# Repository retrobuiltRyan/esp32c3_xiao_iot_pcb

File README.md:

# esp32c3_xiao_iot_pcb
PCB for MQTT projects. Sensor, I2C screen, rotary encoder input, RGB LEDs, and buck converter breakout for the ESP32 C3 XIAO dev board.

| Project Difficulty | Rating |
|----------|--------|
| **Hardware Difficulty** | ●● Easy |
| **Software Complexity** | ●● Easy? | 

 <br>
This is the ~$5 [ESP32c3 XIAO microcontroller](https://www.digikey.com/en/products/detail/seeed-technology-co-ltd/113991054/16652880) (with its antenna on the left) variant.

### Example Projects

Three-ish example projects are shown using this PCB:

- 1.1 – WiFi Clock
- 1.2 – Basic "Dumb" Clock
- 1.3 – Countdown Timer
- 2.0 – Weather Station with Terminal-Style Display
- 3.0 – Current (120V AC) Probe Monitor over MQTT

## 1.1 WiFi Clock
 <br>
 <br>

Large digit (70mm height) 7-segment clock. Connects to 2.4 GHz WiFi and grabs time from HTTP "google.com" TCP port 80. Previously grabbed time from NTP, but I have found some enterprise networks do not like this traffic and block the device.  

Files for the [RGB LED 7-segment digit PCB](https://github.com/retrobuiltRyan/Neo7Segment-Design-Files). You'll need to make four (each digit needs qty 29 RGB LEDs).  

A Daylight Saving Time function is implemented; however, every 6 months I find this doesn't work as expected, and 6 months between bug testing is annoying, so YMMV. DST compensation works better on Network Time Protocol grabs, but again, some networks do not like this.  

The body is 3D printed. The digit diffusion layer can be experimented with in material color and thickness. (about 0.2)

## 1.2 Dumb Clock (no WiFi)
 <br>

Same hardware, different code for a regular clock that keeps time without WiFi. Hours and minutes are set using the rotary encoder & push button.  

UI Flow:  
BOOT → SET HOURS → SET MINUTES → SET COLOR → RUN  
While in RUN → (press) BRIGHTNESS → Return  
Long press resets clock to 12:00  

## 1.3 Countdown Timer
Task Master style countdown timer. 
UI Flow:
BOOT → brightness adjust + pulsing 00:00 →press [set min] press→ [set hr] →press [start]
Time starts out green color and gradually changes to red as 00:00 time approaches.

## 2.0 Weather Station
 <br>

Calls API: https://api.weather.gov/points/40.4406,-79.9959. Then grabs weather forecast data from https://api.weather.gov/gridpoints/PBZ/78,66/forecast. A bunch of forecast data is returned in JSON text format.  The lat and long point to Pittsburgh, PA, which can be changed. This weather API is a free government service available in the USA only, one benefit is no need for API key. Code then parses only the first five forecast 'periods' to save SRAM and prints over serial (for debug) and to OLED in a terminal-style display using this [2.4 inch OLED screen](https://www.aliexpress.us/item/3256805914521312.html).  
Forecast updates every hour. 3D printed body is stylized as a classic Mac if it was extra wide.  

## 3.0 Current Probe Monitor over MQTT
 <br>
(add a dashboard pic when I get that done) <br>

It's lunchtime and you're starving, but there might be a line for the microwave and toaster! Three minutes for someone's Factor meal to cook?! Wouldn't you like to know if these appliances are available before walking to the office kitchen? What if you could check a dashboard that monitors microwave and toaster oven usage?  

Two contactless probes (current clamp) monitor current draw (0–10A) of both appliances and report their status over MQTT. A dashboard logs usage history and can provide a bunch of interesting data on office lunchtime habits. Could also be deployed as an online monitor for critical infrastructure like deep freezers or coolant pumps—useful things. A temperature and humidity sensor (SHT45) is populated on this PCB to also report ambient conditions as a baseline data point. The SHT45 is a very tiny SMD part; adding this is advanced soldering (you need that stencil ordered).

## PCB BoM
| Reference | Value | Qty | DigiKey P/N |
|-----------|-------|----:|--------------|
| BZ1 | Buzzer_5V | 1 | |
| C1, C3, C4, C5, C6, C8, C10 | 0.1uF 50V | 7 | 1276-1068-1-ND |
| C2, C7, C9, C11 | 0.22uF 50V CER | 4 | 445-2283-1-ND |
| D1 | WS2812B | 1 | [aliexpress](https://www.aliexpress.us/item/3256802466699315.html) |
| D5, D6, D7 | LED | 3 | 1080-1419-1-ND |
| D8 | D | 1 | S5AC-FDICT-ND |
| D9 | SMF15A | 1 | SMF15A-E3-08CT-ND |
| J1 | Barrel_Jack 2.1 × 5.5mm | 1 | EJ508A-ND |
| J2, J5, J6, J7, J10 | Screw_Terminal_2_P3.50mm | 5 | 732-2747-ND |
| Q1 | MOSFET P-CH 30V 25A TO252 | 1 | 785-1106-1-ND |
| Q2 | MMBT2222A | 1 | MMBT2222ATPMSCT-ND |
| Q3 | AO3400A | 1 | 785-1000-1-ND |
| R1 | 220 | 1 | 311-220FRCT-ND |
| R2, R3, R5, R6 | 1K | 4 | 311-1.00KFRCT-ND |
| R4 | 3.3K | 1 | 311-3.30KFRCT-ND |
| R7 | 100k | 1 | 311-100KFRCT-ND |
| R8, R9 | 10K | 2 | 311-10.0KFRCT-ND |
| RN1 | 10k array | 1 | CAY16-103J4LFCT-ND |
| RN4 | 200 array | 1 | CAY16-201J4LFCT-ND |
| SW1 | RotaryEncoder_Switch_MP | 1 | PEC11R-4220F-S0024-ND |
| U1 | MAX40200AUK | 1 | 175-MAX40203AUK+TCT-ND |
| U2 | MP1584_Buck | 1 |[aliexpress](https://www.aliexpress.us/item/3256805684077964.html) |
| U3 | L7805 | 1 | 497-7255-1-ND |
| U7 | ESP32C3 | 1 | 1597-113991054-ND |
| U8 | UCC27511ADBV | 1 | 296-49474-1-ND |
| U9 | SHT4x | 1 | 1649-SHT45-AD1B-R2CT-ND |

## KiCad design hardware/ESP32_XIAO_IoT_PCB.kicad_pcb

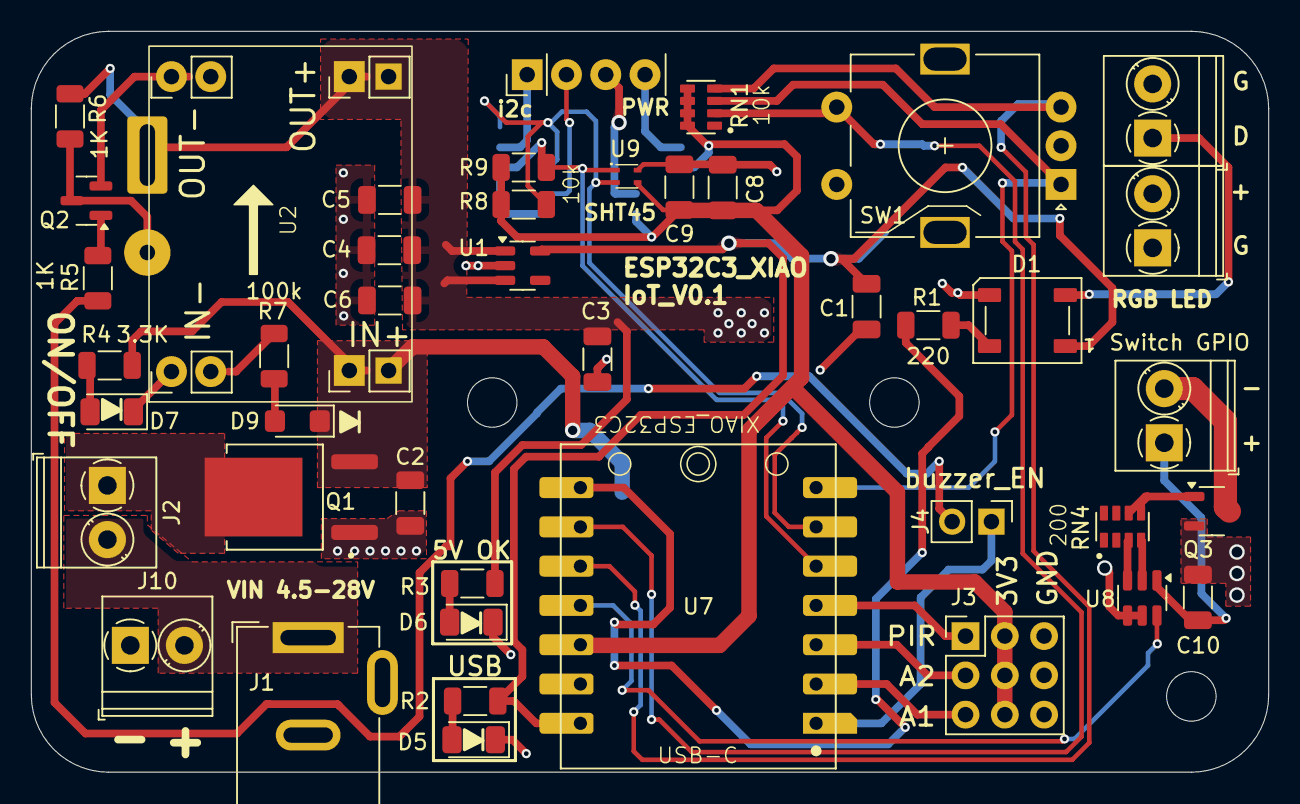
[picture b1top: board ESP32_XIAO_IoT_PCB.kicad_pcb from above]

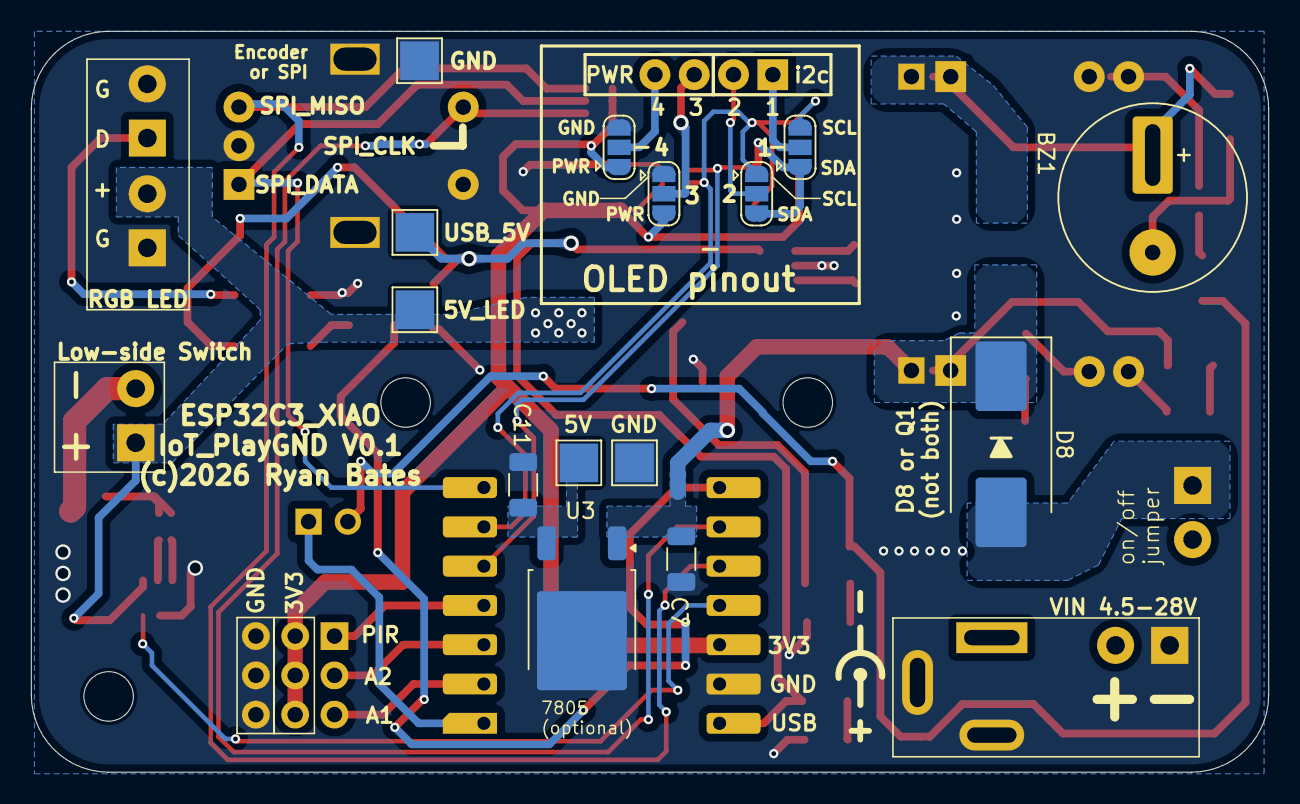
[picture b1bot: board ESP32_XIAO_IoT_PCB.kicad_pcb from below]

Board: 2 copper layers, 80.0 x 47.9 mm, 60 parts (14 on the bottom side), 36 nets.

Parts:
BZ1: Buzzer_5V; MagneticBuzzer_ProSignal_ABT-410-RC
C1, C3, C4, C5, C6, C8, C10: 0.1uF 50V; C_1206_3216Metric
C2, C7, C9, C11: 0.22uF 50V CER; C_1206_3216Metric
D1: WS2812B; LED_WS2812B_PLCC4_5.0x5.0mm_P3.2mm
D5, D6, D7: LED; LED_1206_3216Metric
D8: D; D_SMC_Handsoldering
D9: SMF15A; D_SMF
H1, H2, H3: MountingHole_M3; MountingHole_3.2mm_M3
J1: Barrel_Jack; BarrelJack_GCT_DCJ200-10-A_Horizontal
J2, J5, J6, J7, J10: Screw_Terminal_2_P3.50mm; TerminalBlock_Phoenix_PT-1,5-2-3.5-H_1x02_P3.50mm_Horizontal
J3: ServoPort_03; ServoPort_03_Vertical
J4: PINHD_1x2_Male; PinHeader_1x02_P2.54mm_Vertical
J9: PINHD_1x4_Male; PinHeader_1x04_P2.54mm_Vertical
JP2, JP4, JP7, JP8: SolderJumper_3_Open; SolderJumper-3_P1.3mm_Open_RoundedPad1.0x1.5mm
Q1: MOSFET P-CH 30V 25A TO252; MOSFET_P-CH_30V_25A_TO252
Q2: MMBT2222A; SOT-23
Q3: AO3400A; SOT-23-3
R1: 220; R_1206_3216Metric
R2, R3, R5, R6: 1K; R_1206_3216Metric
R4: 3.3K; R_1206_3216Metric
R7: 100k; R_1206_3216Metric
R8, R9: 10K; R_1206_3216Metric
RN1: 10k array; CAT16-4_R-Array_1206
RN4: 200 array; CAT16-4_R-Array_1206
SW1: RotaryEncoder_Switch_MP; RotaryEncoder_Alps_EC11E-Switch_Vertical_H20mm
TP2, TP3, TP4, TP5, TP6: TestPoint; TestPoint_Pad_2.5x2.5mm
U1: MAX40200AUK; SOT-23-5
U2: MP1584_Buck; MP1584
U3: L7805; TO-252-2
U7: ESP32C3; esp32c3_xiao_seeed_studio
U8: UCC27511ADBV; SOT-23-6
U9: SHT4x; SHT4X

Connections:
3V3: C8.1, C9.1, J3.VCC, JP7.3 (B), JP8.3 (B), R8.1, R9.1, RN1.5 (R4.2), RN1.6 (R3.2), RN1.7 (R2.2), RN1.8 (R1.2), U7.12 (VCC_3V3), U9.3 (VDD)
5V_LED: BZ1.1, C3.1, C4.1, C5.1, C6.1, C10.2, J6.2, J7.1, R3.1, R6.1, TP4.1, U1.1 (VDD), U1.3 (EN), U2.5 (OUT+), U2.6 (OUT+), U8.1 (V_{DD})
5V_OUT: C11.1, TP2.1, U3.3 (OUT)
+BATT: J1.1, J2.2, J10.2
/1: J9.1, JP2.2 (C)
/2: J9.2, JP4.2 (C)
/3: J9.3, JP7.2 (C)
/4: J9.4, JP8.2 (C)
/Analog1: J3.3 (IN3), U7.2 (GPIO3[D1])
/Analog2: J3.2 (IN2), U7.3 (GPIO4[D2])
/BATT_IN: D8.2 (A), J2.1, Q1.2 (S)
/BATT_IN+: C2.1, C7.1, D8.1 (K), D9.1 (A1), Q1.3 (D), R4.1, U2.3 (IN+), U2.4 (IN+), U3.1 (IN)
/Buzzer: J4.2, R5.1
/MOSFET_A_DRAIN: J7.2, Q3.3 (D)
/MOSFET_DRV_A: U7.11 (GPIO10/MOSI[D10]), U8.6 (IN+)
/PIR: J3.1 (IN1), U7.4 (GPIO5[D3])
/RGB_DATA: R1.2, U7.8 (GPIO20/RX[D7])
/SPI_CLK: RN1.2 (R2.1), SW1.S1, U7.9 (GPIO8/SCK[D8])
/SPI_DATA: RN1.3 (R3.1), SW1.A, U7.7 (GPIO21/TX[D6])
/SPI_MISO: RN1.4 (R4.1), SW1.B, U7.10 (GPIO9/MISO[D9])
/i2c+: JP2.1 (A), JP4.1 (A), R8.2, U7.6 (GPIO7/SCL[D5]), U9.2 (SCL)
/i2c-: JP2.3 (B), JP4.3 (B), R9.2, U7.5 (GPIO6/SDA[D4]), U9.1 (SDA)
GND: C1.2, C2.2, C3.2, C4.2, C5.2, C6.2, C7.2, C8.2, C9.2, C10.1, C11.2, D1.3 (VSS), D5.1 (K), D6.1 (K), D7.1 (K), J1.2 (GND), J3.GND, J5.2, J6.1, J10.1, JP7.1 (A), JP8.1 (A), Q1.1 (G), Q2.2 (E), Q3.2 (S), R7.2, SW1.C, SW1.MP, SW1.S2, TP3.1, TP5.1, U1.2 (GND), U2.1 (IN-), U2.2 (IN-), U2.7 (OUT-), U2.8 (OUT-), U3.2 (GND), U7.13 (GND), U8.4 (GND), U8.5 (IN-), U9.4 (VSS)
unnamed: D1.4 (DIN), R1.1
unnamed: D1.2 (DOUT), J5.1
unnamed: D5.2 (A), R2.2
unnamed: D6.2 (A), R3.2
unnamed: D7.2 (A), R4.2
unnamed: D9.2 (A2), R7.1
unnamed: Q2.1 (B), R5.2
unnamed: BZ1.2, Q2.3 (C), R6.2
unnamed: Q3.1 (G), RN4.5 (R4.2), RN4.6 (R3.2)
unnamed: RN4.3 (R3.1), U8.3 (OUTL)
unnamed: RN4.4 (R4.1), U8.2 (OUTH)
unnamed: J4.1, U7.1 (GPIO2[D0])
USB_5V: C1.1, D1.1 (VDD), R2.1, TP6.1, U1.5 (OUT), U7.14 (VUSB)

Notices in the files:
hardware/ESP32_XIAO_IoT_PCB.kicad_pcb:
(c)2026 Ryan Bates
